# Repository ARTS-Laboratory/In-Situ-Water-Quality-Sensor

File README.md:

# In-Situ-Water-Quality-Sensor
An in situ water quality sensor for monitoring water quality from a UAV-deployable sensor package. The sensor packages provide real-time monitoring of pH, conductivity, temperature, and turbidity. 

<p align="center">
 <br> 
UAV deployment mechanism as of June 2025.
</p>

<p align="center">
 <br> 
UAV deployment mechanism as of June 2024.
</p>

<p align="center">
 <br> 
System configuration as of June 2024 used for testing UAV deployments. 
</p>

<p align="center">
 <br> 
System configuration as of August 2023 used for testing UAV deployments. 
</p>

<p align="center">
 <br> 
An early configuration of the proposed UAV-deployable in situ water quality system with pedal-style solar panels. 
</p>

## [System Design](system_design)
The system (hardware and software) design for the project.

## Licensing and Citation

This work is licensed under a Creative Commons Attribution-ShareAlike 4.0 International License [cc-by-sa 4.0].

Cite this data as: 

#### Bibtex

@Misc{ARTSLabSituWaterQuality,    
  author = {{ARTS-L}ab},  
  howpublished = {GitHub},  
  title  = {In-Situ-Water-Quality-Sensor},  
  groups = {ARTS-Lab},    
  url    = {https://github.com/ARTS-Laboratory/In-Situ-Water-Quality-Sensor},   
  note = {Accessed: Month dd, yyyy},   
}

<p align="center">
QR code for repo.

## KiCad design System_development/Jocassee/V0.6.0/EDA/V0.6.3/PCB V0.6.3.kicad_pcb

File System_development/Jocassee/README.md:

# Jocassee
An in situ water quality sensor for monitoring water quality

## V0.1
1. Measures pH and turbidity 
1. Saves data to SD card
1. Water-tight case 
1. This is a general dump of all the initial files. 

## V0.2
1. This is just a clean-up version of 0.1. 
1. The pads on the 1026 resistors are too small
1. move the SMA connection over.
1. Need to add a ground plane to V0.3.
1. Need to add the SMA footprint on V0.3.

## V0.3
1. New designs for PCB boards. 

## V 0.4.0
1. Includes part designs necessary to assemble the water sensor package.
2. Missing probe protector.
3. Missing Apple air tag mount.
4. Need to adjust hold positioning for Solar Flap Fixture.

## V 0.4.5 
1. Includes 2 component holders. One for TDS and pH, and another for TDS, pH, and Turbidity.
2. Includes a probe protector that prevents damage to the ends of the probes.
3. Updated solar flaps to house solar flaps wired in parallel
4. Solar Flap Fixture Cap updated to include a spot for Apple air tag
5. Updated Solar Flap Fixture. (position for holes moved, height extended, and inside tabs reduced from 4 to 2)
6. Need to make these parts out of solid plastic pieces and leak-test the package.
7. PCB Design includes RTC Module and Micro SD Card Module.
8. The PCB includes Footprints for the PH, TDS, and Turbidity Sensors.
9. Updated Arduino code to Measure the PH, TDS, and Turbidity of the water.
10. The code controls the sampling time and saves the collected data on a micro SD card.

## V 0.4.6 
1. These are general updates and a major reorganization of all the files in V0.4.5.
2. The updated PCB design includes footprints pH, Turbidity, TDS, and Temperature sensors.
3. The Updated Arduino code.
4. The Kriging Code

## V 0.4.7
1. The updated PCB design includes footprints for a GPS Module
2. Updated Arduino Code to include GPS readings
3. Added multiple designs for 3D printed Buoys
5. Added a design for a cap that includes a spot to attach an antenna
6. Included STL files and G-code for each buoy and cap.
7. Added an assembly to better size 3D printed parts for the Chassis
8. Added a Bill of Matirials

## V 0.5.0
### Version of Refrence for "UAV-Deployable Sensor Nodes for Spatial and Temporal In-Situ Water Quality Monitoring and Mapping", Burnett et al. 2025
 1. Minor changes to chassis to more densly pack the sensors
 2. Minor Buoy/drop mechanism design revisions
 3. Minor changes to PCB mounting screw holes

## V 0.5.1
### Usability upgrades on V 0.5.0
    
## V 0.6.0
1. Updated PCB design including GPS, wireless module and latest compact signal conditioning boards for pH & TDS sensing.
2. Includes an easily dettachable solar buoy for increased operational endurance.
3. Includes waterproof connector for solar power input and battery charging from external sources.
4. Contains a BMS for effecient battery charging and load sharing.
5. Features a capless design where O'ring is used to seal the top opening.
6. Includes step files for every components used in sensor node.

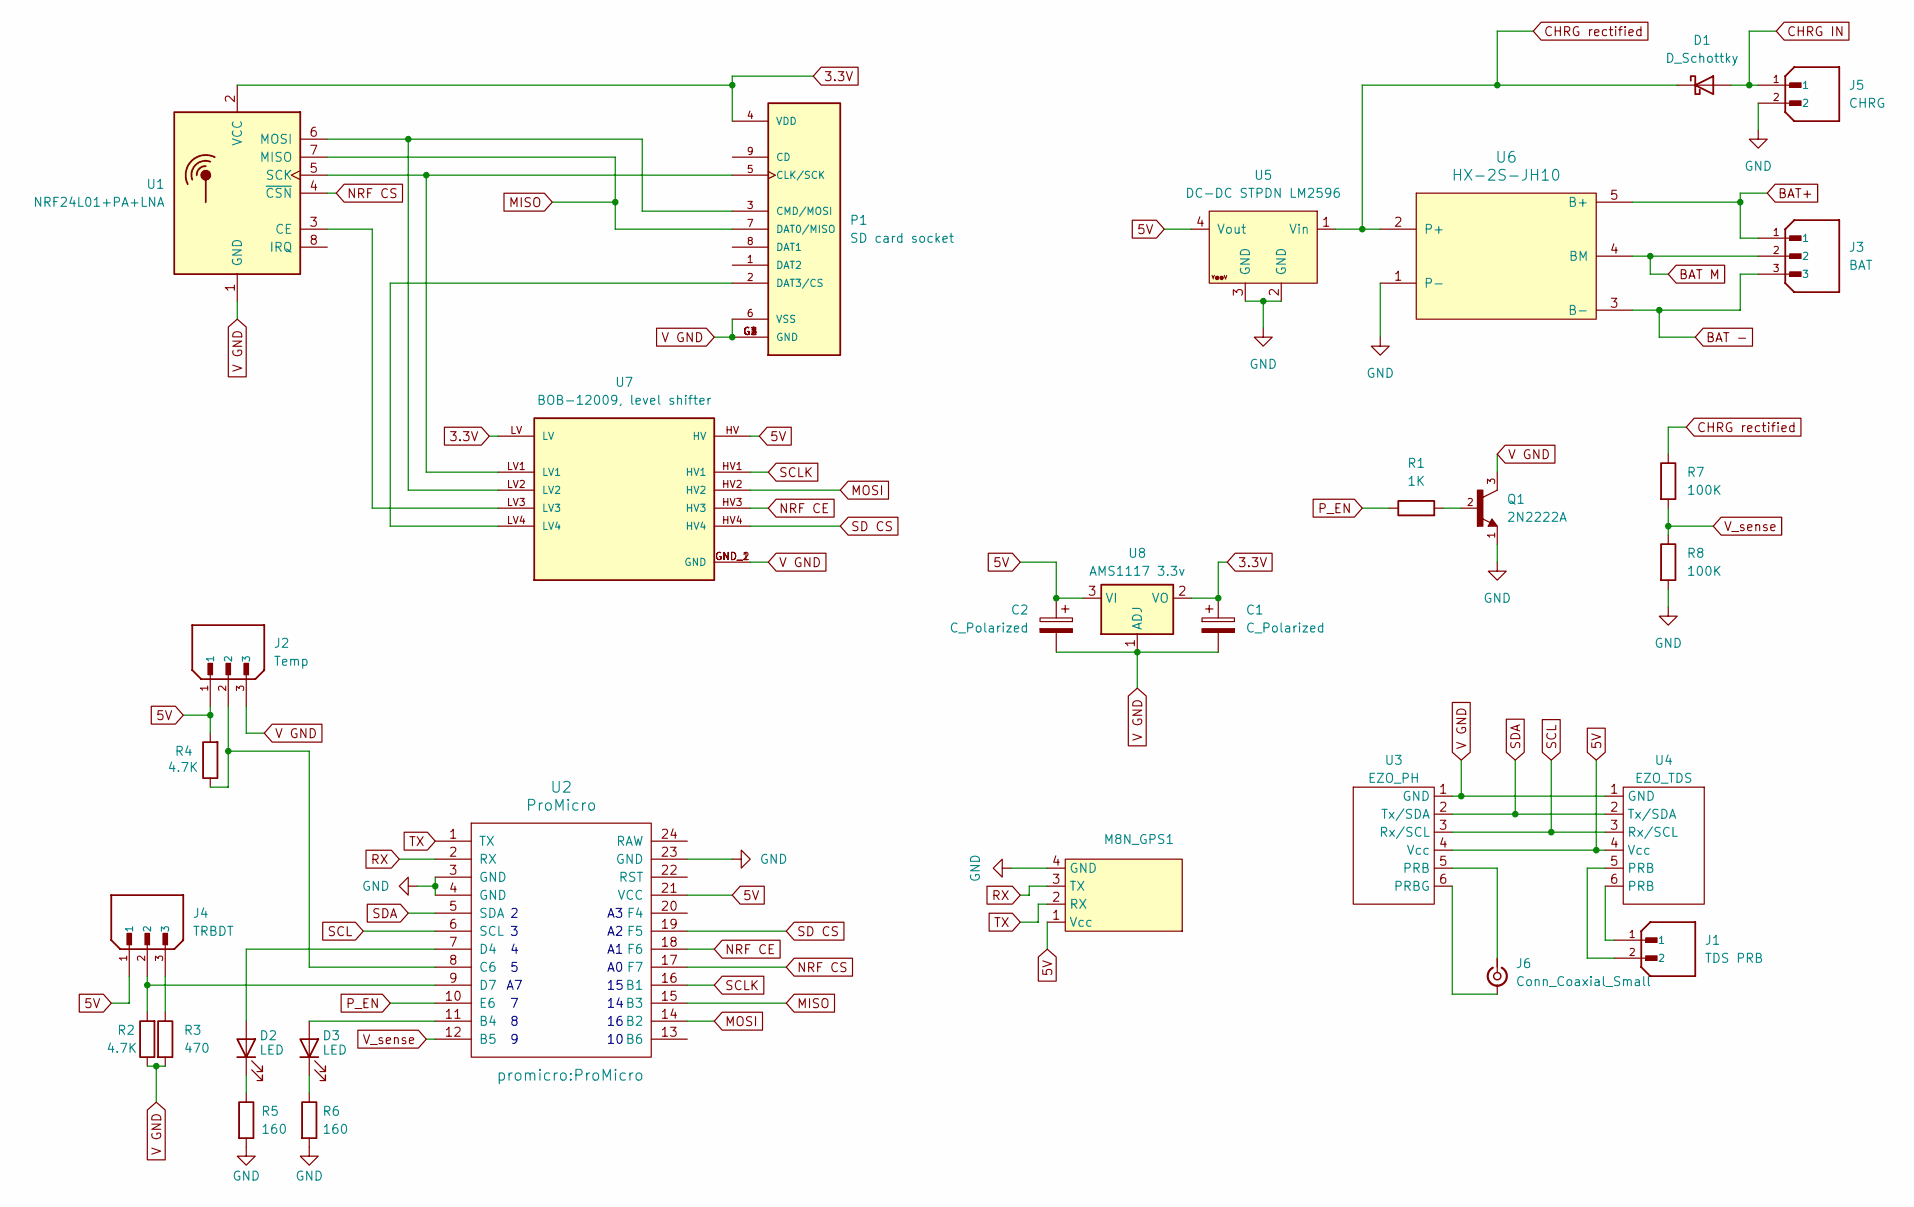
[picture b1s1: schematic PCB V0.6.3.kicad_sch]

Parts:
C1, C2: C_Polarized; CP_Radial_D4.0mm_P2.00mm
D1: D_Schottky; D_DO-34_SOD68_P7.62mm_Horizontal
D2, D3: LED; LED_D3.0mm
J1: TDS PRB; JST_B2B-XH-A_LF__SN_; PARTREV N/A
J2: Temp; XH2.54; PARTREV 7/4/21
J3: BAT; XH2.54; PARTREV 7/4/21
J4: TRBDT; XH2.54; PARTREV 7/4/21
J5: CHRG; JST_B2B-XH-A_LF__SN_; PARTREV N/A
J6: Conn_Coaxial_Small; SMA_Amphenol_901-143_Horizontal
M8N_GPS1: Ublox_Neo_M8N_GPS
P1: SD card socket; SUNTECH_ST-TF-003A
Q1: 2N2222A; TO92254P470H750-3; PARTREV N/A
R1: 1K; R_Axial_DIN0204_L3.6mm_D1.6mm_P5.08mm_Horizontal
R2: 4.7K; R_Axial_DIN0204_L3.6mm_D1.6mm_P7.62mm_Horizontal
R3: 470; R_Axial_DIN0204_L3.6mm_D1.6mm_P7.62mm_Horizontal
R4: 4.7K; R_Axial_DIN0204_L3.6mm_D1.6mm_P5.08mm_Horizontal
R5, R6: 160; R_Axial_DIN0204_L3.6mm_D1.6mm_P7.62mm_Horizontal
R7, R8: 100K; R_Axial_DIN0204_L3.6mm_D1.6mm_P5.08mm_Horizontal
U1: NRF24L01+PA+LNA; NRF24L01+PA/LNA-FOOTPRINT
U2: ProMicro
U3: EZO_PH
U4: EZO_TDS
U5: DC-DC STPDN LM2596; YAAJ_DCDC_StepDown_LM2596
U6: HX-2S-JH10
U7: BOB-12009, level shifter; Logic_level_shifter; PARTREV 01
U8: AMS1117 3.3v; SOT-223-3_TabPin2

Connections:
3.3V: C1.1, P1.4 (VDD), U1.2 (VCC), U7.LV, U8.2 (VO)
5V: C2.1, J2.1, J4.1, M8N_GPS1.1 (Vcc), R4.2, U2.21 (VCC), U3.4 (Vcc), U4.4 (Vcc), U5.4 (Vout), U7.HV, U8.3 (VI)
BAT -: J3.3, U6.3 (B-)
BAT M: J3.2, U6.4 (BM)
BAT+: J3.1, U6.5 (B+)
CHRG IN: D1.2 (A), J5.1
CHRG rectified: D1.1 (K), R7.1, U5.1 (Vin), U6.2 (P+)
GND: J5.2, M8N_GPS1.4 (GND), Q1.1, R5.2, R6.2, R8.2, U2.3 (GND), U2.4 (GND), U2.23 (GND), U5.2 (GND), U5.3 (GND), U6.1 (P-)
MISO: P1.7 (DAT0/MISO), U1.7 (MISO), U2.15 (B3)
MOSI: U2.14 (B2), U7.HV2
NRF CE: U2.18 (F6), U7.HV3
NRF CS: U1.4 (~CSN), U2.17 (F7)
unnamed: D2.2 (A), U2.7 (D4)
unnamed: D2.1 (K), R5.1
unnamed: D3.2 (A), U2.11 (B4)
unnamed: D3.1 (K), R6.1
unnamed: J1.1, U4.6 (PRB)
unnamed: J1.2, U4.5 (PRB)
unnamed: J4.3, R3.1
unnamed: J6.2 (Ext), U3.6 (PRBG)
unnamed: J6.1 (In), U3.5 (PRB)
unnamed: P1.5 (CLK/SCK), U1.5 (SCK), U7.LV1
unnamed: P1.3 (CMD/MOSI), U1.6 (MOSI), U7.LV2
unnamed: P1.2 (DAT3/CS), U7.LV4
unnamed: Q1.2, R1.2
unnamed: U1.3 (CE), U7.LV3
unnamed: J2.2, R4.1, U2.8 (C6)
unnamed: J4.2, R2.2, U2.9 (D7)
P_EN: R1.1, U2.10 (E6)
RX: M8N_GPS1.3 (TX), U2.2 (RX)
SCL: U2.6 (SCL), U3.3 (Rx/SCL), U4.3 (Rx/SCL)
SCLK: U2.16 (B1), U7.HV1
SD CS: U2.19 (F5), U7.HV4
SDA: U2.5 (SDA), U3.2 (Tx/SDA), U4.2 (Tx/SDA)
TX: M8N_GPS1.2 (RX), U2.1 (TX)
V GND: C1.2, C2.2, J2.3, P1.6 (VSS), P1.G1 (GND), P1.G2 (GND), P1.G3 (GND), P1.G4 (GND), Q1.3, R2.1, R3.2, U1.1 (GND), U3.1 (GND), U4.1 (GND), U7.GND_1 (GND), U7.GND_2 (GND), U8.1 (ADJ)
V_sense: R7.2, R8.1, U2.12 (B5)

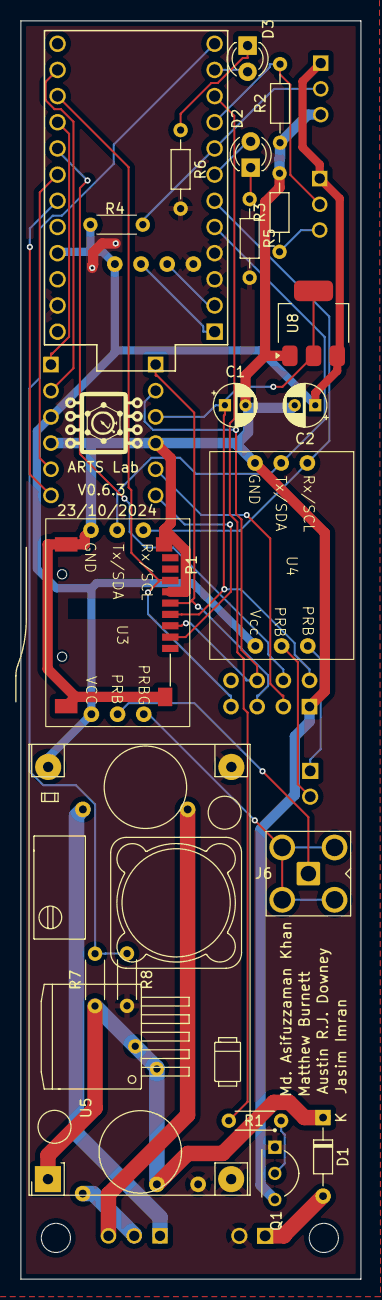
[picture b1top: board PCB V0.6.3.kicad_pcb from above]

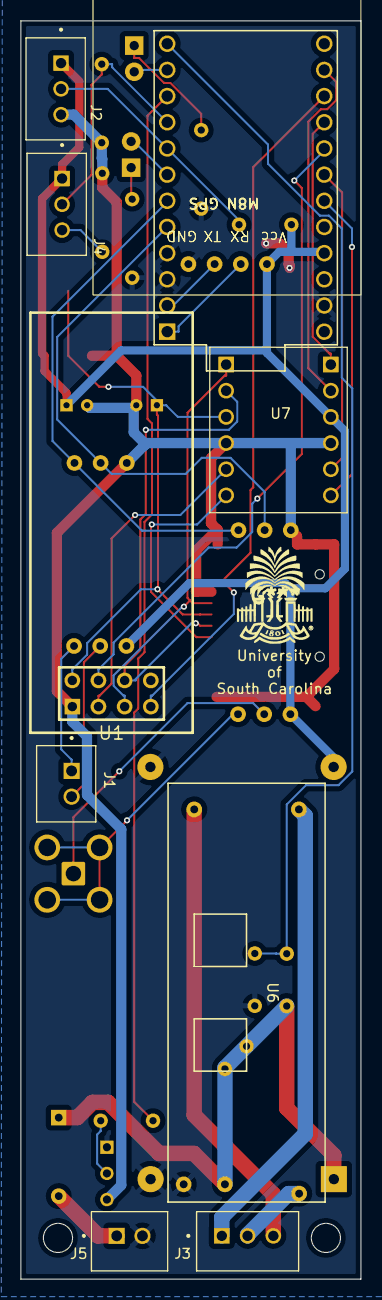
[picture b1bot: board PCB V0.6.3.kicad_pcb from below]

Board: 2 copper layers, 33.0 x 122.1 mm, 31 parts (9 on the bottom side), 37 nets.

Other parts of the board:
ARTS Lab: LOGO

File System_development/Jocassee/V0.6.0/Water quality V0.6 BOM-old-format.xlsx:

PCB Reference | Component | Qty | Unit cost (USD) | Net cost (USD) | Source
C1,C2 | Polarized Capacitor | 2 | 0.59 | 1.18 | digikey
D1 | Schottky Diode | 1 | 0.31 | 0.31 | digikey
D3 | 3mm LED red | 1 | 0.18 | 0.18 | digikey
D2 | 3mm LED green | 1 | 0.26 | 0.26 | digikey
J2,J3,J4 | 3pin XH2.54 male connector | 3 | 0.19 | 0.57000000000000006 | digikey
J1,J5 | 2pin XH2.54 male connector | 2 | 0.14000000000000001 | 0.28000000000000003 | digikey
J6 | SMA connector for pH probe | 1 | 4.8499999999999996 | 4.8499999999999996 | digikey
M8N_GPS1 | Ublox_Neo_M8N_GPS | 1 | 12.74 | 12.74 | eBay
P1 | SD card socket | 1 | 2.54 | 2.54 | digikey
Q1 | 2N2222A/BC337 BJT or equivalent | 1 | 0.22 | 0.22 | digikey
R1 | 1K ohm resistor | 1 | 0.1 | 0.1 | digikey
R2,R4 | 4.7K ohm resistor | 2 | 0.1 | 0.2 | digikey
R3 | 470 ohm resistor | 1 | 0.1 | 0.1 | digikey
R5,R6 | 160/220 ohm resistor | 2 | 0.1 | 0.2 | digikey
R7,R8 | 100K ohm resistor | 2 | 0.1 | 0.2 | digikey
U1 | NRF24L01+PA+LNA | 1 | 2.5 | 2.5 | eBay
U2 | Arduino ProMicro | 1 | 19.5 | 19.5 | digikey
U3 | EZO_PH circuit | 1 | 45.99 | 45.99 | atlas
U4 | EZO_TDS circuit | 1 | 67.989999999999995 | 67.989999999999995 | atlas
U5 | DC-DC Stepdown converter LM2596 | 1 | 1.85 | 1.85 | eBay
U6 | HX-2S-JH10 BMS | 1 | 2.15 | 2.15 | eBay
U7 | BOB-12009, 5V to 3.3V level shifter | 1 | 3.5 | 3.5 | digikey
U8 | AMS1117 3.3v regulator SOT-223-3L | 1 | 0.63 | 0.63 | digikey
N/A | SMA female to male extension cable | 1 | 8.2799999999999994 | 8.2799999999999994 | eBay
N/A | 2s Lipo battery 7.4V (87 x 33 x 20 mm) | 1 | 11.7 | 11.7 | eBay
N/A | Waterproof JST Connector | 2 | 2.58 | 5.16 | eBay
N/A | Solar panels | 9 | 7.39 | 66.509999999999991 | digikey
 |  |  | Total | 259.68999999999994
Some nice to have items but not mandatory
 | 40 pin Female header connector 2.54mm | 1 | 1.0900000000000001 | 1.0900000000000001 | digikey
 | 40 pin Male header connector 2.54mm | 1 | 1.59 | 1.59 | digikey
 | USB to serial converter module | 1 | 2.75 | 2.75 | eBay
 |  |  | Total | 5.43

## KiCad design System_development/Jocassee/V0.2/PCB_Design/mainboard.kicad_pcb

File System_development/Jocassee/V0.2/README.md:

# V1

## Case design
1. Three o-rings
1. 3D printed end caps
1. PCV case
1. Solar Wing
1. Turbidity Case
1. Solar Connection

## PCB Design
1. pH sensor on mezzanine board 
1. Real-time clock on PCB
1. MicroSD adapter for data collection
1. Battery slot for powering the PCB
1. CR1025 battery for Real-time clock
1. Rails for connecting to the turbidity PCB

## Code
1. Records data
1. Calibration done on the micro-controller.

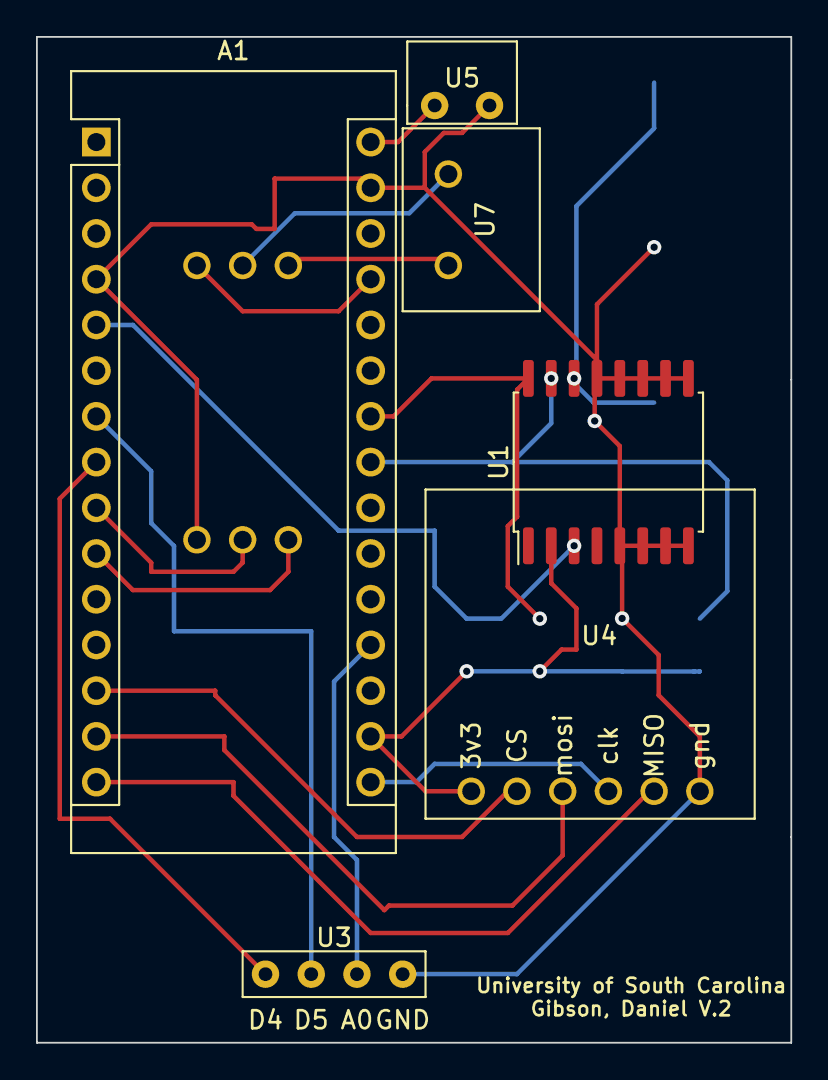
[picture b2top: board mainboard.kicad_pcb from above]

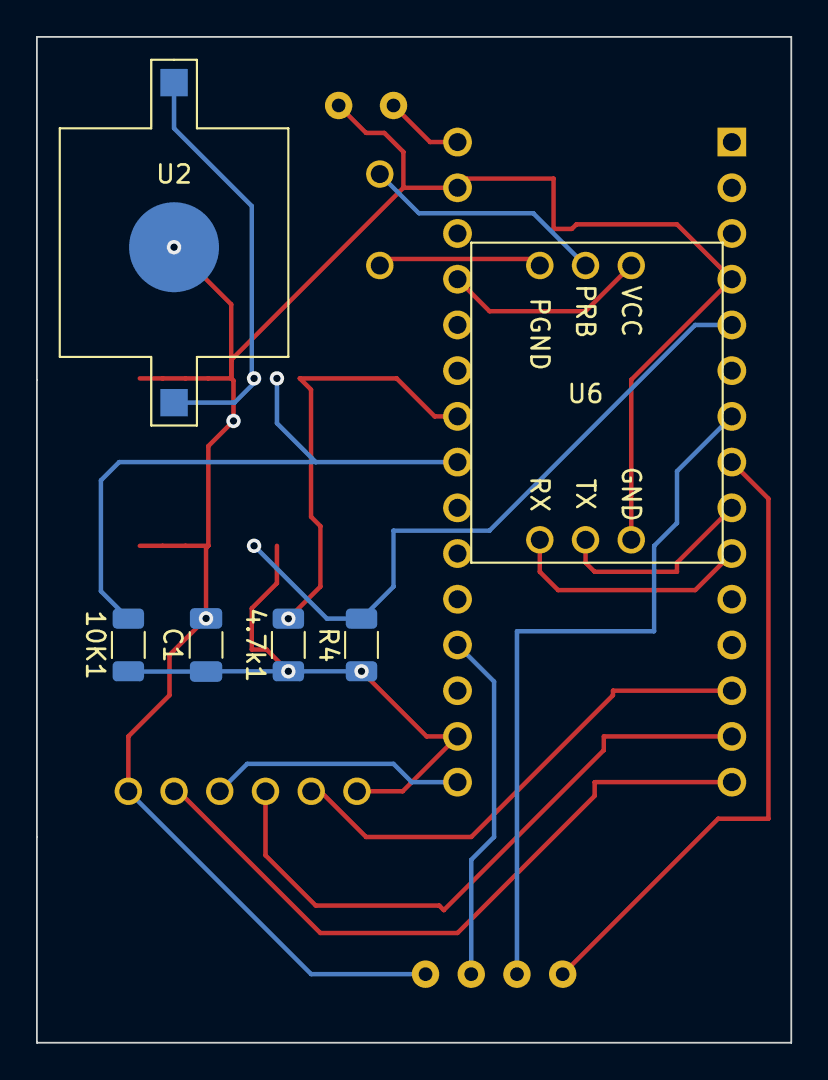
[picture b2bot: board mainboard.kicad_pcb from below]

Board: 2 copper layers, 41.9 x 55.9 mm, 12 parts (6 on the bottom side), 19 nets.

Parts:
4.7k1, 10K1: R; R_1206_3216Metric
A1: Arduino_Nano_v3.x; Arduino_Nano
C1: C; C_1206_3216Metric
R4: 4.7K; R_1206_3216Metric
U1: DS3231M; SOIC-16W_7.5x10.3mm_P1.27mm
U2: CR1025
U3: Rails
U4: MicroSD.V2
U5: Battery; battery
U6: Ph_embedded; pH_embedded
U7: Probe_slot; Probe_rails

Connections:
GND: A1.4, A1.29, C1.2, U1.5, U1.6, U1.7, U1.8, U1.9, U1.10, U1.11, U1.12, U1.13, U2.3, U3.4, U4.6, U5.2, U6.1
unnamed: 4.7k1.2, A1.24, U1.16
unnamed: 4.7k1.1, 10K1.1, A1.17, C1.1, R4.1, U1.2, U4.1
unnamed: 10K1.2, A1.23, U1.15
unnamed: A1.5, R4.2, U1.3
unnamed: A1.7, U3.2
unnamed: A1.8, U3.1
unnamed: A1.9, U6.2
unnamed: A1.10, U6.3
unnamed: A1.13, U4.2
unnamed: A1.14, U4.3
unnamed: A1.15, U4.5
unnamed: A1.16, U4.4
unnamed: A1.19, U3.3
unnamed: A1.27, U6.4
unnamed: A1.30, U5.1
unnamed: U1.14, U2.1, U2.2
unnamed: U6.5, U7.1
unnamed: U6.6, U7.2

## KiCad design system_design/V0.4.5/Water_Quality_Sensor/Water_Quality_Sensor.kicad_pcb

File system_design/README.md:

# in-Situ Water Quality Sensor Package system design
V0.4.6 system design includes:

<p align="center">
Figure 1: Sensor package mission algorithm breakdown.
</p>

<p align="center">
Figure 2: (a) Designed Footprints of the PCB, (b) The Front Side of the PCB, and
 (c) Back Side of the PCB.
</p>

<p align="center">
Figure 3: The tray that holds the sensor package's internal components.
</p>

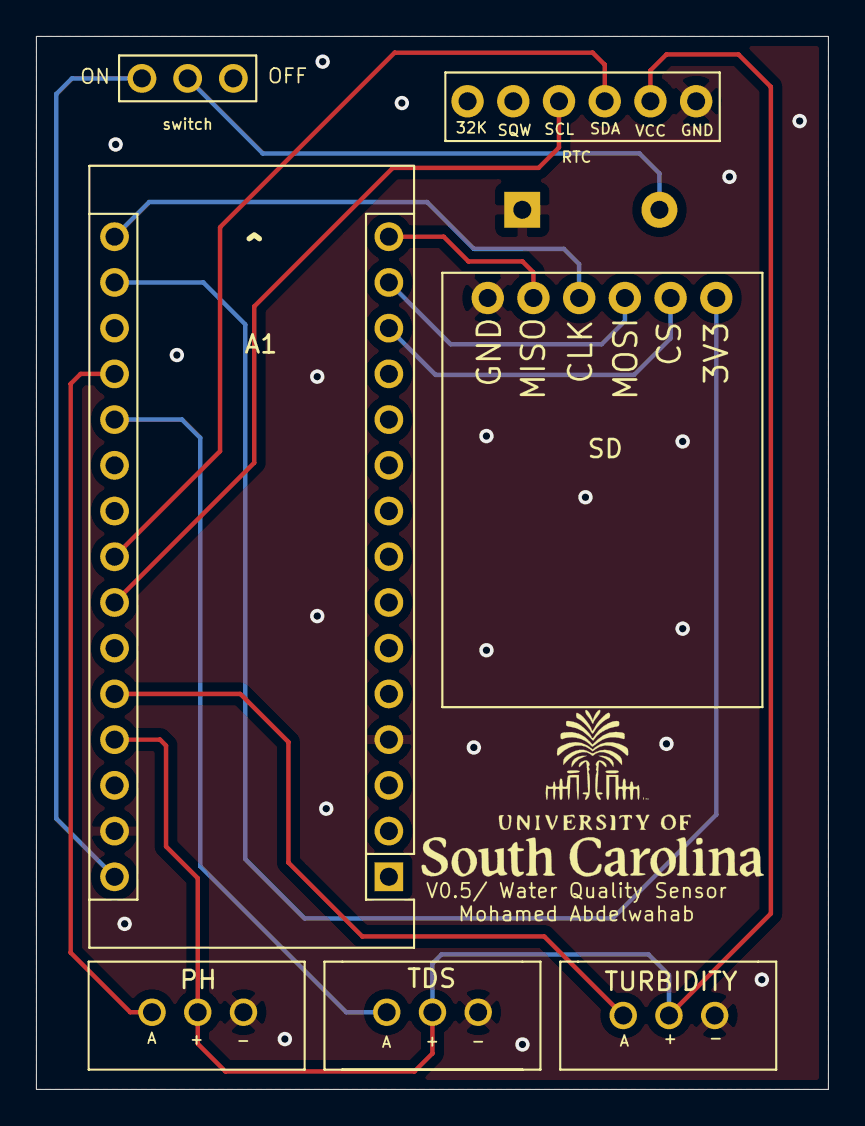
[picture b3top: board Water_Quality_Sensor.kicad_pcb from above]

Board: 2 copper layers, 44.0 x 58.5 mm, 9 parts (1 on the bottom side), 14 nets.

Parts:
A1: Arduino_Nano_v3.x; Arduino_Nano
R1: R; uofsc_logo_0_75in
U2: SD
U3: BATTERY; battery_input
U4: SWITCH; slide_switch
U5: PH; phraails
U6: TURBIDITY; turbidity_rails
U7: TDS; sensor_rails
U8: RTC

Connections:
GND: A1.4, A1.29, U2.6, U3.2, U5.3, U6.3, U7.3, U8.6
unnamed: A1.13, U2.2
unnamed: A1.14, U2.3
unnamed: A1.15, U2.5
unnamed: A1.16, U2.4
unnamed: A1.17, U2.1
unnamed: A1.19, U5.1
unnamed: A1.20, U7.1
unnamed: A1.23, U8.4
unnamed: A1.24, U8.3
unnamed: A1.26, U6.1
unnamed: A1.27, U5.2, U6.2, U7.2, U8.5
unnamed: A1.30, U4.3
unnamed: U3.1, U4.2

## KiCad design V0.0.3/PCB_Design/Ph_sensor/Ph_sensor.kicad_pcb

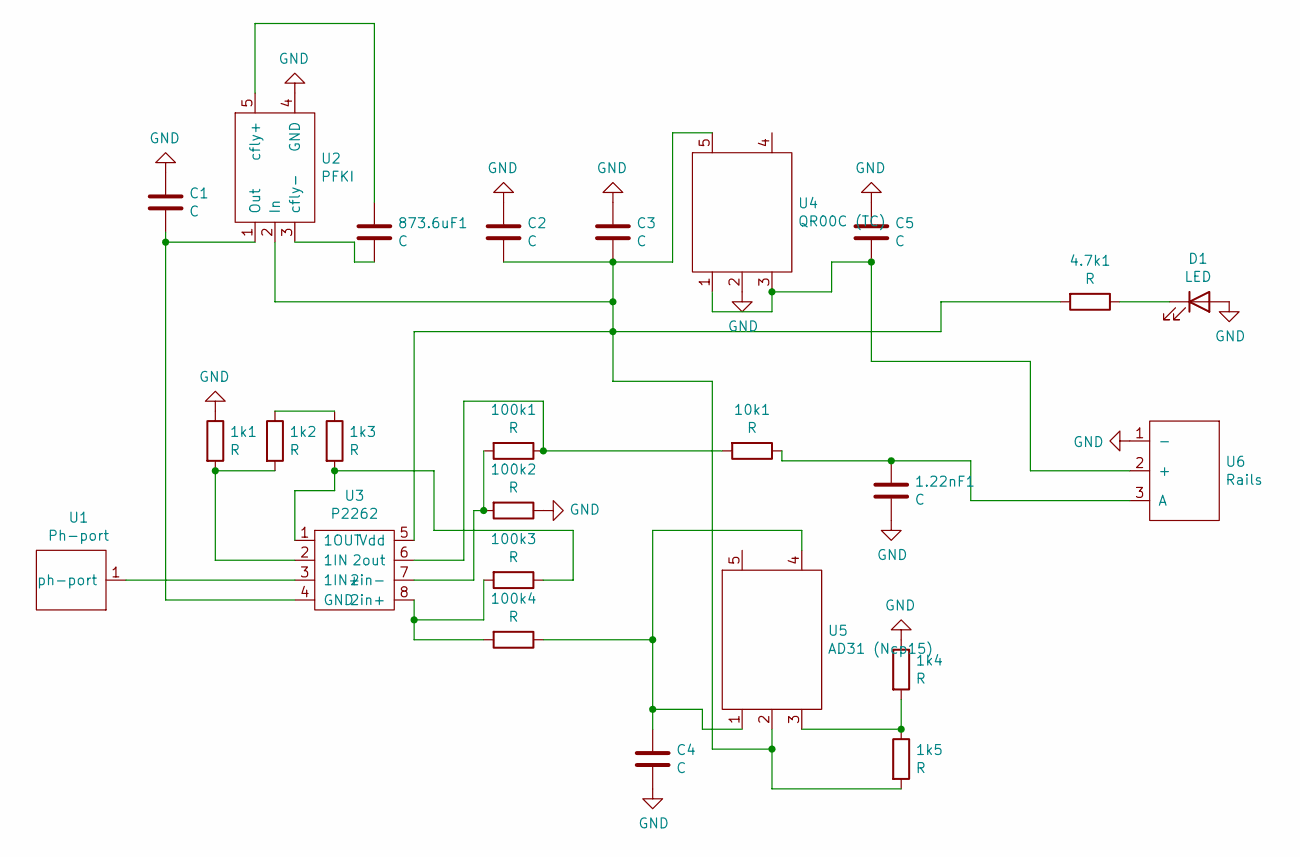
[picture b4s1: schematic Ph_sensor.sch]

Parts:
1.22nF1, 873.6uF1: C; C_0603_1608Metric
1k1, 1k2, 1k3, 1k4, 1k5, 4.7k1, 10k1, 100k1, 100k2, 100k3, 100k4: R; R_0603_1608Metric
C1, C2, C3, C4, C5: C; C_0603_1608Metric
D1: LED; LED_0603_1608Metric
U1: Ph-port; pH_port
U2: PFKI
U3: P2262
U4: QR00C (TC); PFKI
U5: AD31 (Ncp15); PFKI
U6: Rails

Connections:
GND: 1.22nF1.2, 1k1.1, 1k4.1, 100k2.1, C1.1, C2.1, C3.1, C4.2, C5.1, D1.2 (A), U2.4 (GND), U4.2, U6.1 (-)
unnamed: 1.22nF1.1, 10k1.1, U6.3 (A)
unnamed: 1k1.2, 1k2.2, U3.2 (1IN)
unnamed: 1k2.1, 1k3.1
unnamed: 1k4.2, 1k5.1, U5.3
unnamed: 1k5.2, 4.7k1.2, C2.2, C3.2, U2.2 (In), U3.5 (Vdd), U4.5, U5.2
unnamed: 4.7k1.1, D1.1 (K)
unnamed: 10k1.2, 100k1.1, U3.6 (2out)
unnamed: 100k1.2, 100k2.2, U3.7 (2in-)
unnamed: 1k3.2, 100k3.1, U3.1 (1OUT)
unnamed: 100k3.2, 100k4.2, U3.8 (2in+)
unnamed: 100k4.1, C4.1, U5.1, U5.4
unnamed: 873.6uF1.1, U2.5 (cfly+)
unnamed: 873.6uF1.2, U2.3 (cfly-)
unnamed: C1.2, U2.1 (Out), U3.4 (GND)
unnamed: C5.2, U4.1, U4.3, U6.2 (+)
unnamed: U1.1, U3.3 (1IN+)

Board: 2 copper layers, 25 parts (0 on the bottom side), 17 nets, no tracks yet.

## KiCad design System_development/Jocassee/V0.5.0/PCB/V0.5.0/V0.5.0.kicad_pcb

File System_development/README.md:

# Sensor Package Variations  
Sensor package variations are named after freshwater lakes in South Carolina. 

## Jocassee
* Sensor package designed for data acquisition with onboard data storage and wireless data transmission. 

## Marion 
* Sensor package designed with edge AI capabilities.

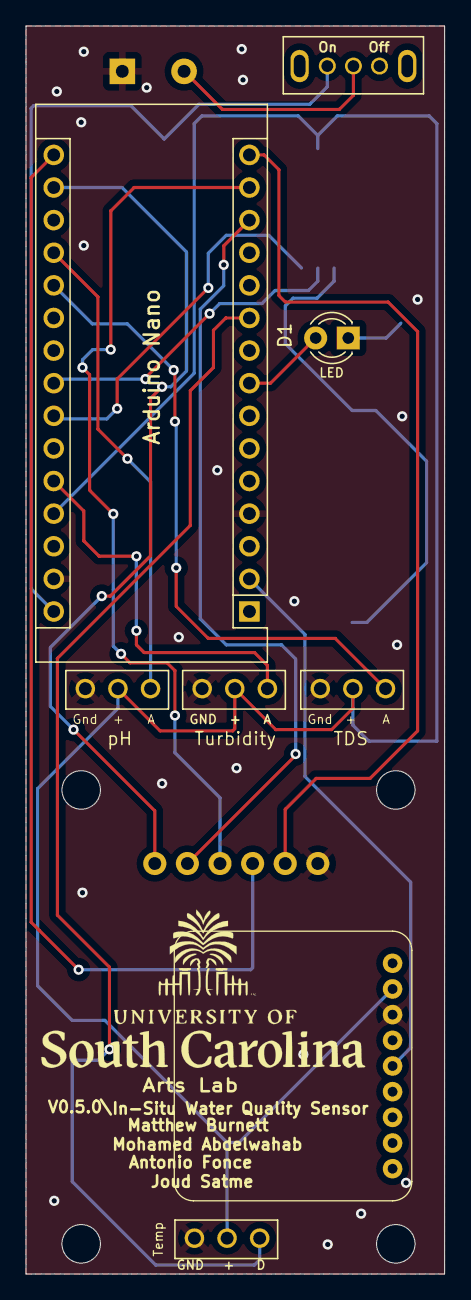
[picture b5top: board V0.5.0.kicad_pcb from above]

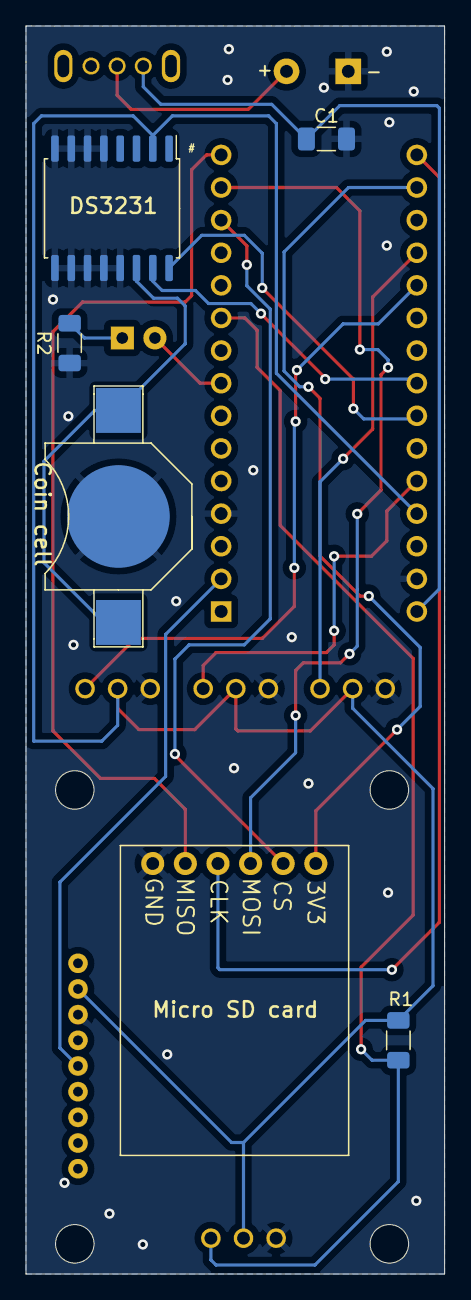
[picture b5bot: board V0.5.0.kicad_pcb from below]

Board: 2 copper layers, 32.6 x 97.2 mm, 15 parts (7 on the bottom side), 19 nets.

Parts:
A1: Arduino_Nano_v3.x; Arduino_Nano
BT1: Battery_Cell; battery_holder_10mm
C1: C; C_1206_3216Metric_Pad1.33x1.80mm_HandSolder
D1: LED; LED_D3.0mm
R1, R2: R; R_1206_3216Metric_Pad1.30x1.75mm_HandSolder
U1: water_Battery; Battery_Input
U2: SD
U3: switch; grounded_switch
U4: pH; phraails
U5: Sensor; TDS
U6: DS3231M; SOIC-16W_7.5x10.3mm_P1.27mm
U7: Sensor; Turbidity
U8: Temp; Temp.
U9: GPS Module

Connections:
GND: A1.4 (GND), A1.29 (GND), BT1.2 (-), C1.2, R2.2, U1.2 (Gnd), U2.6 (GND), U4.1 (GND), U5.1 (GND), U6.5 (GND), U6.6 (GND), U6.7 (GND), U6.8 (GND), U6.9 (GND), U6.10 (GND), U6.11 (GND), U6.12 (GND), U6.13 (GND), U7.1 (GND), U8.1 (Gnd), U9.7 (GND)
unnamed: A1.17 (3V3), U2.1 (3V)
unnamed: A1.27 (+5V), R1.2, U4.2 (+), U5.2 (+), U6.2 (VCC), U7.2 (+), U8.2 (5V), U9.8 (VIN)
unnamed: A1.19 (A0), U4.3 (A)
unnamed: A1.20 (A1), U5.3 (A)
unnamed: A1.23 (A4), U6.15 (SDA)
unnamed: A1.24 (A5), U6.16 (SCL)
unnamed: A1.26 (A7), U7.3 (A)
unnamed: A1.2 (D0/RX), U9.5 (TX)
unnamed: A1.8 (D5), D1.2 (A)
unnamed: A1.10 (D7), R1.1, U8.3 (D)
unnamed: A1.13 (D10), U2.2 (CS)
unnamed: A1.14 (D11), U2.3 (Mosi)
unnamed: A1.15 (D12), U2.5 (Miso)
unnamed: A1.16 (D13), U2.4 (CLK)
unnamed: A1.30 (VIN), C1.1, U3.3 (PO)
unnamed: BT1.1 (+), U6.14 (VBAT)
unnamed: D1.1 (K), R2.1
unnamed: U1.1 (Power), U3.2 (PI)

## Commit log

2021-10-15 first update
2021-10-15 updated file name
2021-10-15 V0.0.1\Case_design
2021-10-15 V0.0.1
2021-10-15 created v.0.0.3
2021-11-04 Gibson, Daniel
2022-02-18 Rename PHTEST.CSV to PHTEST(48hr).CSV
2022-03-21 clean up the files
2022-03-21 folder updates
2022-03-21 changes made to layout
2022-05-05 cleaned up files.
2022-05-24 added image
2022-05-24 deleted picture
2022-06-17 V0.5
2022-06-18 Water Quality Sensor V0.5
2022-06-18 Water Quality Sensor
2022-06-21 Water Quality sensor V0.4.5 update
2022-06-21 Water Quality Sensor V0.4.5
2022-06-21 Water Quality Sensor PCB
2022-06-21 added v0.4.6
2022-06-27 Water Quality Sensor fusion 360 files
2022-06-30 v0.4.6
2022-06-30 Water_Quality_Sensor V0.4.6
2023-05-26 Updated PCB design and Arduino cpde
2023-06-21 PCB & Battery Tray CAD Design
2023-08-13 Updated layout and main readme
2023-08-13 figure
2023-08-13 update fiure
2023-08-15 The Kriging Code
    By Matlab
2023-08-15 Kriging Code
2023-08-15 System Design Files for V0.4.6
2024-05-03 Cleaned up repo layout, added high-level versions.
2024-05-12 removed un-needed folders
2024-06-13 Added GPS
    Added a GPS module to the PCB board
2024-06-17 Made Bouy and Hinge and Leaf cad files
2024-06-17 Updated Bill of Materials and added Buoy 2
2024-06-17 Updated the Water Sensor Buoy models
2024-06-17 Updated Claps for Buoys
2024-06-17 Uploaded STL files
2024-06-20 Media For ReadMe
2024-06-24 Update README.md
    Updated the README.md for V0.4.7
2024-06-24 Added another Buoy design and reorganized files
    Added another buoy design and an assembly to better scale the buoys. Also reorganized the files to include only what is needed.
2024-06-24 Removed files for V0.4.7 from V0.4.6
    Removed files meant for V0.4.7 from V0.4.6 after accidental inclusion
2024-06-24 Added Buoy 3 and 4
    Added designs for water sensor buoys 3 and 4
2024-06-24 Fixed Buoy 4
    Fixed the inner radius on the Buoy 4
2024-06-26 Updated Buoy and cap designs
    Updated the buoy designs to have thinner walls and updated the cap design to have O-ring slots. Also added all buoys to the Chassis Assembly.
2024-07-01 Updated Cad Files
    Updated the CAD files for the Water Sensor Cap and PCB tray, added Buoys 5, 6, and 7. Updated BOM
2024-07-02 Updated PCB Tray and BOM
2024-07-10 Made CAD assembly of water sensor chassi with components
    Made an assembly with the water sensor chassi including all the components except the buoy. Added a new folder for this addition and reorganized other folders.
2024-07-12 Changed PCB tray
    Made PCB tray longer and added a Battery tray insert. Also separated PCB tray into a bottom and top parts for ease of use. Added a Cad model for spacers for PCB. Updated Arc sensor and water sensor c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
2024-07-15 Updated PCB tray and Water Sensor Cap
2024-07-17 Updated PCB board tray, Spacer for PCB, and Water Sensor Cap
2024-07-19 Made Printable Grate and Buoys 11 and 12
    Made a Printable Grate and Buoys 11 and 12. Updated Assembly, PCB spacers, and PCB tray. removed Plug as it is no longer needed.
2024-07-20 Updated PCB tray, Printable Grate, and Water Sensor Cap
2024-07-22 Added a V0.5.0 folder and reorganized files
    Updated the files to include a V0.5.0 folder and reorganized the files.
2024-07-22 added STL files for printable parts
2024-07-28 Updated PCB tray, Assembly
2024-07-30 Shortened Pipe
2024-08-04 Gen Updates
2024-08-07 Grate
2024-08-08 Cad Model Updates and BOM
2024-08-08 Figures
2024-10-03 Added V0.6.0
2024-10-03 Update README.md
    Added V0.6.0 description
2024-10-04 Updated full assembly & added sensors
2024-10-06 added different buoy versions
2024-10-12 Added groove for antenna and connector on PCB tray's top face
2024-10-12 added initial PCB design files
2024-10-18 New PCB prototype added
2024-10-21 PCB routing done
2024-10-23 PCB V0.6.3 added
2024-10-23 Group members name added in PCB
2024-10-23 some aesthetic changes
2024-10-25 PCB refined
2024-10-26 Updated BOM & added PCB mounting holes in tray
2024-10-26 deleted draft bom
2024-10-27 V0.5.0 PCB Update
2024-10-29 Switch connections added
2024-11-01 Full assembly image added
2024-11-02 Solar panels added in BOM, Buy now have holes for wires
2024-11-05 replaced Amazon parts with eBay
2024-11-08 Src price changed to USD only
2024-11-18 Panel wiring instructions added
2025-01-14 BOM updated
2025-01-24 added QR code
2025-01-29 Code folders created
2025-02-05 Minor modifications on CAD
2025-02-10 MCU pin notation corrected.
2025-02-19 OS code updated
2025-02-21 OS edit
2025-02-24 OS code edited
2025-02-27 Serial less version added
2025-03-11 buoy design updated
2025-03-18 code modified
2025-03-24 code folder organized
2025-04-02 OS updated
2025-04-07 OS code cleaned up
2025-05-30 V 0.5 PCB errors corrected
2025-05-30 added 2025 sensor setup
2025-05-30 added png image
2025-05-30 update image
2025-05-30 New buoy version added
2025-06-02 V.05 BOM updated
2025-06-09 V0.5 BOM updated
2025-06-10 BOM v 0.5 updated
2025-06-10 V0.5 PCB refined
2025-06-16 Buoy version 14
    Here has an updated version of a buoy that is I-bolt compatible
2025-06-16 buoy version 14.0.1
    Changed file format to .stl
2025-06-17 changed file name
    nothing actually changed
2025-06-17 testing testing 123
2025-06-18 new buoy cad
    I cadded a new buoy that is a clamshell design (2 parts), designed to work with m4 bolts/washers/nuts. It has holes on the top so expanding foam can be added.
2025-06-18 PCBs updated
2025-06-18 clamshell buoy, version 15.1
    Added an I-bolt connection
2025-06-19 buoy 15.2.5
    Added a sunken nut for the eyebolt
2025-06-19 includes an stl file
    nothing new here, just added an stl file of buoy version 15.2.5 so it can be 3d printed easier
2025-06-20 buoy version 15.5
    fixed some tolerances for the sink in m4 nuts, added a quality of life feature to help with assembly onto the pvc
2025-06-20 2 new versions of buoy
    Includes an expairamental version where I tried to reduce the wall thickness. And a practical version to be printed that does not have a roof and should weigh considerably less then the standard 15.5.
2025-06-20 slightly updated
    now wont give errors when sliced
2025-06-23 buoy version 16
    a new buoy design. Clamshell and eyebolt compatible. Print 2 copies to use for a buoy. Designed to work with m4 bolts, nuts and washers (excluding the eyebolts. Fill the inside with expanding foam
2025-06-24 buoy version 16.5
    changed the location of the eyebolt, slightly thickened the walls
2025-06-24 organizational fixes
    slight fix in organization
2025-06-24 more meaningful organization
    organization work in the buoy folder: organizes first by eyebolt compatibility
    then by clamshell designs and if there is a roof
2025-06-24 pictures of buoy for reference
    Includes 4 different buoy types
2025-06-24 necessary reorganization
2025-06-24 more organization
2025-06-25 edited bolt holes
    ensuring clearance
2025-06-25 slight edits
    changed the nut size
2025-06-26 buoy version 16.5.3
    only aesthetic changes
2025-06-27 Code and BOM updated
2025-07-09 New eyebolt buoy added
2025-07-10 V0.5.1 created
2025-07-17 buoy version 17
    new buoy design. Not eyebolt compatible
2025-07-17 just slight minor edits
2025-07-18 buoy v 17.0.1
    slightly more rounded spot for the rope to go along with Dr. Downey's preferences
2025-07-18 major edits tobuoy
2025-07-18 17.03
2025-07-28 buoy v 17.0.1
    updated hole sizes. Should be ready for larger production
2025-07-28 necessary name change
    to prevent confusion
2025-07-28 RTC issue solved
2025-07-29 buoy 17.0.5
    very slight fix; cleaned up buoy folder
2025-07-29 addition of image
    to update the readme files
2025-08-07 Intro work on shortening 0.5
    a bunch of new cad models for the assembly. Design of shortened 0.5 is incomplete for now.
2025-08-21 Embossing added
2025-08-21 embossing added for printable grate
2025-10-02 updated BOM
2025-10-02 updated BOM location and title
2025-10-17 V0.5.1 code updated
2025-10-20 NTU conversion updated
2025-10-23 Add README for In-Situ Water Quality Sensor
    This README provides detailed instructions for deploying and recovering the In-Situ Water Quality Sensor, including steps for setup, operation, and maintenance.
2025-10-23 Update headings in Readme.md for clarity
2025-10-23 Fix formatting in Readme.md for clarity
2025-11-14 sticker added
2026-06-03 Grate step file created
